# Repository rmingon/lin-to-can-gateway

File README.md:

# Secure LIN-to-CAN Gateway with AES Encryption

This project implements a **custom PCB gateway** that bridges **Local Interconnect Network (LIN)** and **Controller Area Network (CAN)** communication buses. It integrates **AES-based cryptographic software** to ensure secure message transfer across networks, making it suitable for both embedded research and industrial-grade applications.

---

## Features

- **MCU Core:** STM32F107 microcontroller
- **CAN Transceiver:** MCP2551 for reliable CAN bus communication
- **LIN Transceiver:** TJA1020 for LIN bus interface
- **Crypto Layer:** AES software encryption for secure message payloads
- **Voltage Regulation:** On-board LM317 regulator provides stable 3.3V supply
- **Programming & Debugging:** SWD interface for firmware upload and debugging
- **User Interface:** Reset button, status LEDs, and configuration jumper
- **Compact PCB Design:** 2-layer PCB optimized for automotive and embedded systems

---

## Hardware Overview

### Major Components

- **U3 – STM32F107**: 32-bit ARM Cortex-M3 MCU
- **U1 – MCP2551**: High-speed CAN transceiver
- **U4 – TJA1020**: LIN transceiver for automotive communication
- **U2 – LM317**: Adjustable linear regulator, set to 3.3V output
- **Y2**: External crystal oscillator for precise MCU timing

### Connectors

- **J1 / J2**: LIN and CAN bus connections
- **J3**: SWD programming/debugging interface
- **JP1**: Boot configuration jumper

---

## Firmware

The firmware implements:

- LIN message reception, decryption, and forwarding to CAN
- CAN message reception, encryption, and forwarding to LIN
- AES-based payload encryption for secure communication
- Error handling and bus monitoring

---

## Applications

- **Automotive Systems:** Securely bridging LIN and CAN buses in vehicles
- **Industrial Automation:** Protecting data integrity across mixed communication buses
- **IoT Gateways:** Encrypted transport between legacy fieldbuses and modern networks
- **Research & Development:** Testing secure communication protocols in embedded systems

---

## Getting Started

1. **Assemble the PCB** with the provided KiCad files and BOM.
2. **Flash the firmware** via the SWD interface.
3. **Connect LIN and CAN networks** to the respective terminals.
4. **Test secure message transfer** with your chosen CAN/LIN monitoring tools.

---

## License

This project is licensed under the CERN Open Hardware Licence Version 2 - Strongly Reciprocal (CERN-OHL-S v2).

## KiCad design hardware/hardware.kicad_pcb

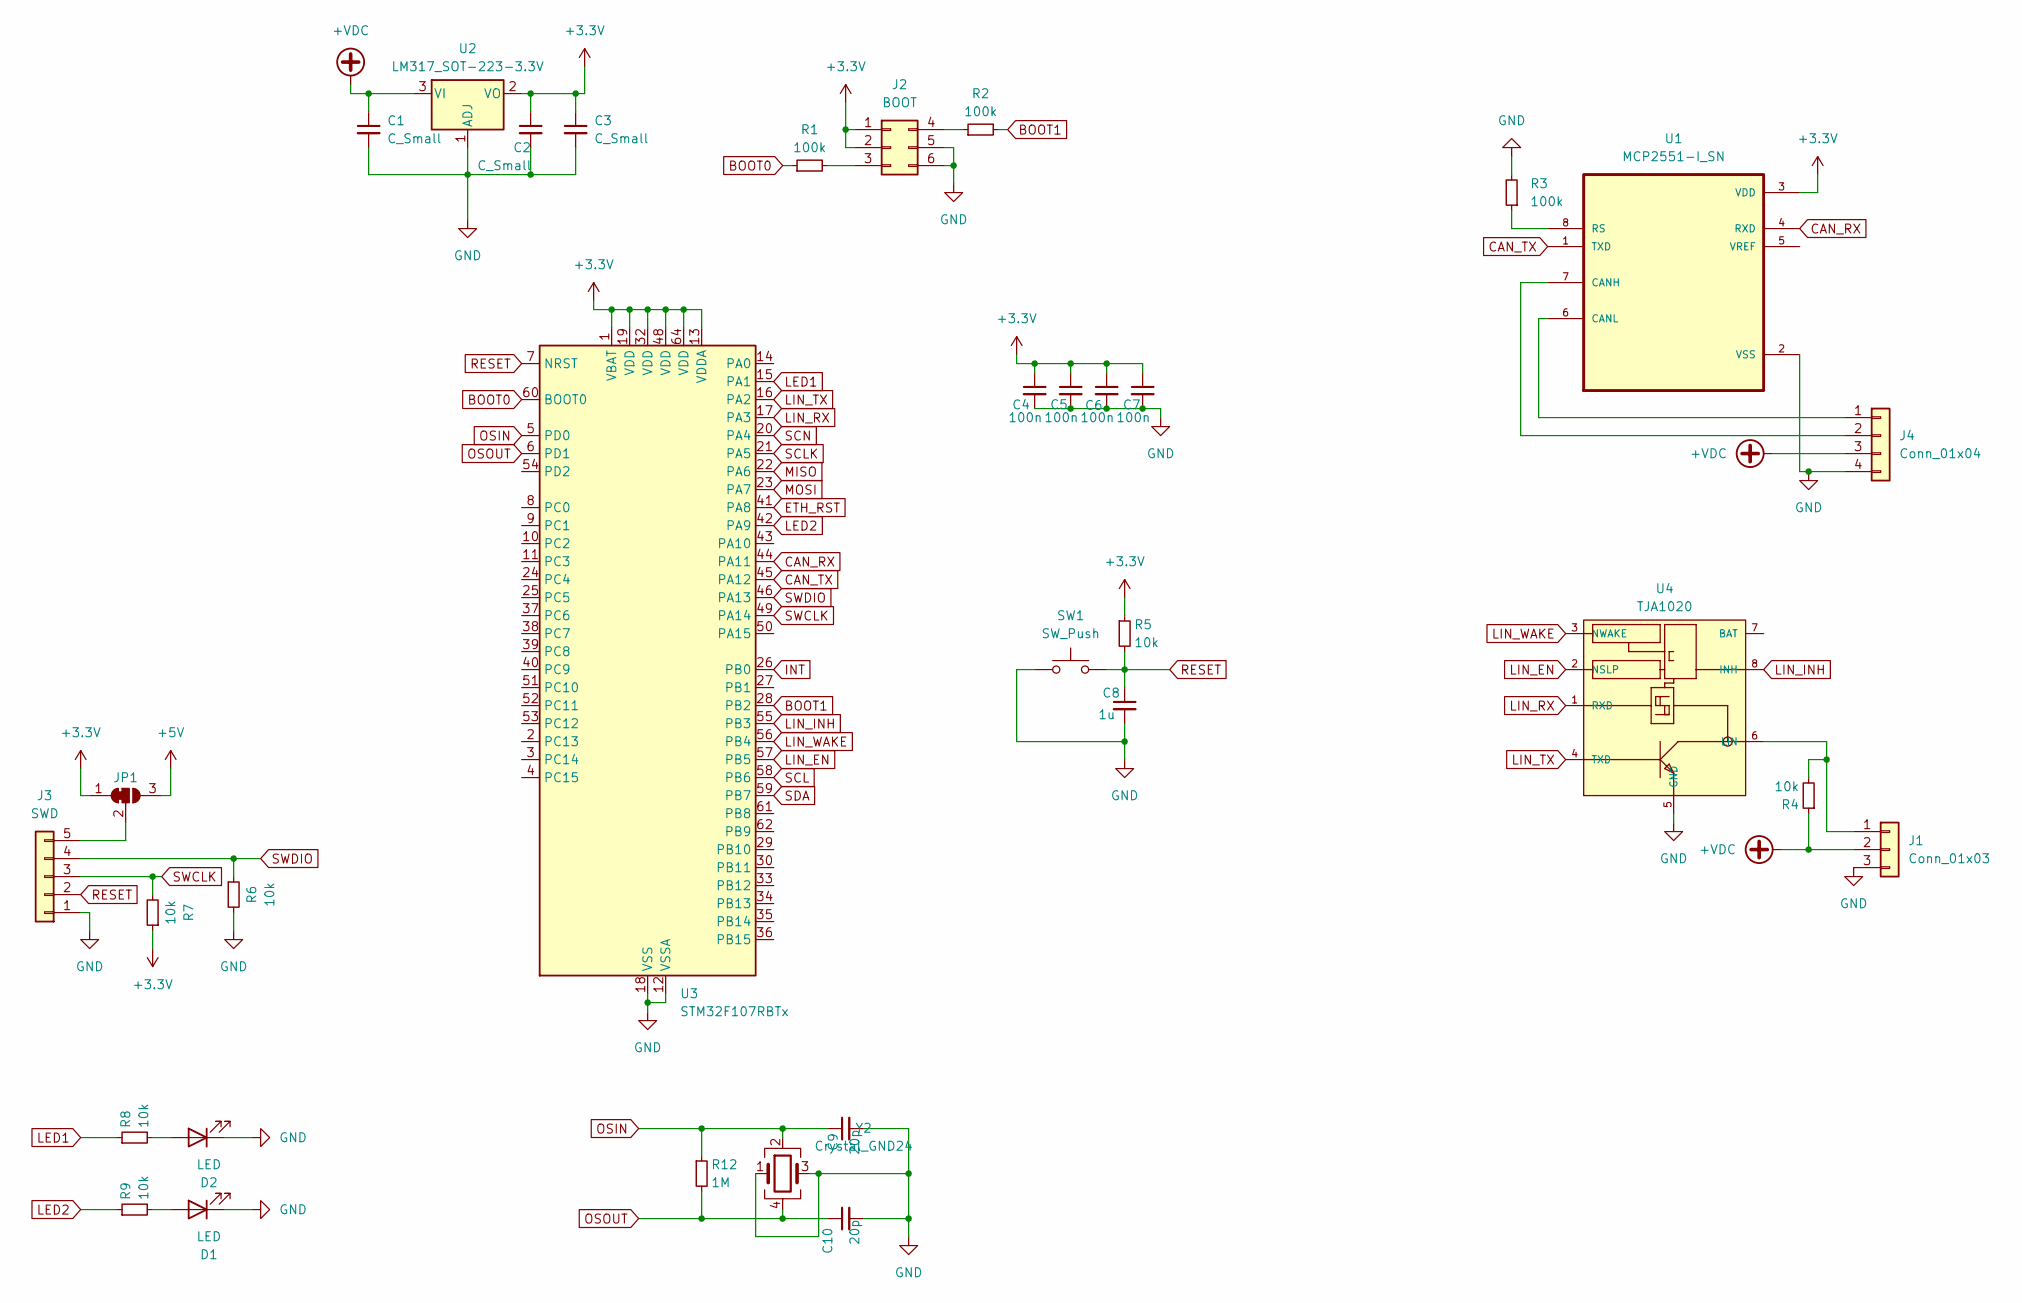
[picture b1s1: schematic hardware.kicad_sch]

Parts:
C1, C2, C3: C_Small; C_0603_1608Metric
C4, C5, C6, C7: 100n; C_0603_1608Metric
C8: 1u; C_0603_1608Metric
C9, C10: 20p; C_0603_1608Metric
D1, D2: LED; D_0603_1608Metric
J1: Conn_01x03; PhoenixContact_MCV_1,5_3-GF-3.5_1x03_P3.50mm_Vertical_Threa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
J2: BOOT; PinHeader_2x03_P2.54mm_Vertical_SMD
J3: SWD; PinHeader_1x05_P2.54mm_Vertical
J4: Conn_01x04; PhoenixContact_MCV_1,5_4-GF-3.5_1x04_P3.50mm_Vertical_Threa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
JP1: SolderJumper_3_Bridged12; SolderJumper-3_P1.3mm_Bridged12_RoundedPad1.0x1.5mm
R1, R2, R3: 100k; R_0603_1608Metric
R4, R5, R6, R7, R8, R9: 10k; R_0603_1608Metric
R12: 1M; R_0603_1608Metric
SW1: SW_Push; SW_SPST_CK_RS282G05A3
U1: MCP2551-I_SN; SOIC127P599X175-8N
U2: LM317_SOT-223-3.3V; SOT-223-3_TabPin2
U3: STM32F107RBTx; LQFP-64_10x10mm_P0.5mm
U4: TJA1020; SO8
Y2: Crystal_GND24; Crystal_SMD_3225-4Pin_3.2x2.5mm

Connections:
+3.3V: C2.1, C3.1, C4.1, C5.1, C6.1, C7.1, J2.1, J2.2, JP1.1 (A), R5.1, R7.1, U1.3 (VDD), U2.2 (VO), U3.1 (VBAT), U3.13 (VDDA), U3.19 (VDD), U3.32 (VDD), U3.48 (VDD), U3.64 (VDD)
+5V: JP1.3 (B)
+VDC: C1.1, J1.2, J4.3, R4.1, U2.3 (VI)
BOOT0: R1.1, U3.60 (BOOT0)
BOOT1: R2.2, U3.28 (PB2)
CAN_RX: U1.4 (RXD), U3.44 (PA11)
CAN_TX: U1.1 (TXD), U3.45 (PA12)
ETH_RST: U3.41 (PA8)
GND: C1.2, C2.2, C3.2, C4.2, C5.2, C6.2, C7.2, C8.2, C9.2, C10.2, D1.1 (K), D2.1 (K), J1.3, J2.5, J2.6, J3.1, J4.4, R3.2, R6.2, SW1.1, U1.2 (VSS), U2.1 (ADJ), U3.12 (VSSA), U3.18 (VSS), U3.31 (VSS), U3.47 (VSS), U3.63 (VSS), U4.5 (GND), Y2.1, Y2.3
INT: U3.26 (PB0)
LED1: R8.1, U3.15 (PA1)
LED2: R9.1, U3.42 (PA9)
LIN_EN: U3.57 (PB5), U4.2 (NSLP)
LIN_INH: U3.55 (PB3), U4.8 (INH)
LIN_RX: U3.17 (PA3), U4.1 (RXD)
LIN_TX: U3.16 (PA2), U4.4 (TXD)
LIN_WAKE: U3.56 (PB4), U4.3 (NWAKE)
MISO: U3.22 (PA6)
MOSI: U3.23 (PA7)
unnamed: D1.2 (A), R9.2
unnamed: D2.2 (A), R8.2
unnamed: J1.1, R4.2, U4.6 (LIN)
unnamed: J2.3, R1.2
unnamed: J2.4, R2.1
unnamed: J3.5, JP1.2 (C)
unnamed: J4.1, U1.6 (CANL)
unnamed: J4.2, U1.7 (CANH)
unnamed: R3.1, U1.8 (RS)
OSIN: C9.1, R12.1, U3.5 (PD0), Y2.2
OSOUT: C10.1, R12.2, U3.6 (PD1), Y2.4
RESET: C8.1, J3.2, R5.2, SW1.2, U3.7 (NRST)
SCL: U3.58 (PB6)
SCLK: U3.21 (PA5)
SCN: U3.20 (PA4)
SDA: U3.59 (PB7)
SWCLK: J3.3, R7.2, U3.49 (PA14)
SWDIO: J3.4, R6.1, U3.46 (PA13)

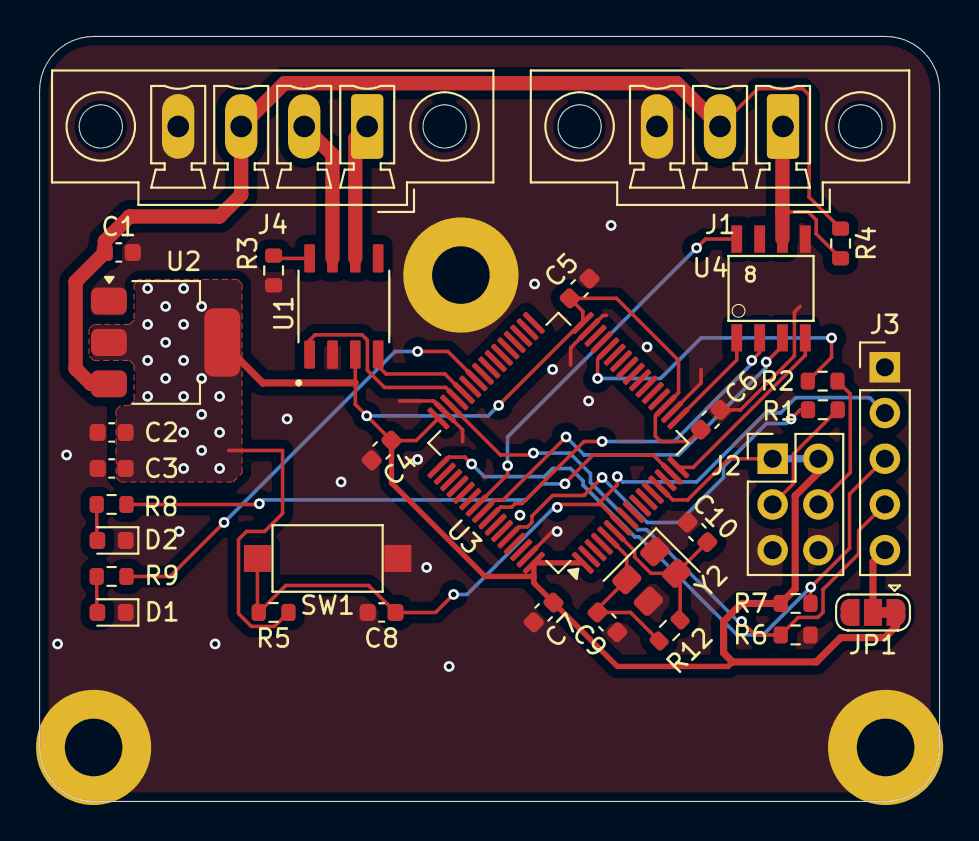
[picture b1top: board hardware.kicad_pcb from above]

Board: 2 copper layers, 50.0 x 42.5 mm, 33 parts (0 on the bottom side), 28 nets.

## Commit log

2025-09-08 add minimal shematic components
2025-09-08 add lin control bus
2025-09-08 add lin + can connectors
2025-09-09 upgrade lin footprint
2025-09-09 fix boot 0 & boot 1 pin
2025-09-10 finish pcb wiring
2025-09-10 add pictures
2025-09-10 add readme
2025-09-10 add licence
